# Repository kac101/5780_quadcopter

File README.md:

<h1 align="center">ECE 5780 - Quadcopter</h1>

<p>
Quadcopter Team Members:
<ul style="list-style-position: inside;">
  <li>Rudis Argueta</li>
  <li>Donggeon Kim </li>
  <li>Taehoon Kim</li>
  <li>Luke Stillings </li>
</ul>
</p>

___

<p align="center" style="font-size:11px;">
Figure 1. GIF Of The Drone Hovering
</p>  

---

## Project Summary
A quadcopter that can only hover made using the Raspberry Pi Pico 2 W, a motor driver, BetaFPV motors, and a MPU6050. 

**How It Works:**
To create a quadcopter using the Raspberry Pi Pico 2W we had to create a motor driver that will power the motors by using a battery, and the PWM signals coming from the Raspberry Pi Pico 2W. The PWM signals control the speed of the motors, and to do this we used a MOSFET that has a low threshold voltage because the max voltage the Pico's PWM will be is 3.3V. Additionally, we used a MPU6050 to grab x, and y information, and with this information we created a PID loop that will attempt to keep the quadcopter at a 0° roll, and pitch rate. Additionally, the frame and drone was assembled by us. 

---

## System Architecture

1. **Power**  
   - 1s LiPo battery -> Power 4x BetaFPV Motors  
   - USB Connection Powers Raspberry Pi Pico 2 W 

2. **Sensing**  
   - MPU6050 → I²C (GPIO 26/27)  
   - Data-ready interrupt (GPIO 22) 

3. **Control**  
   - PID loop 
   - PWM on four channels (GPIO 6–9)
   - Data over serial USB
   - Onboard LED blink marks start/end of each loop  

---

## Development Milestones

### Milestone 1  
- Proto-PCB built to verify MOSFET motor-driver circuit  
- Final PCB layout completed (Pico, MOSFETs, IMU)  
- Component selection and documentation finalized

<p align="center" style="font-size:11px;">
Figure 2. Schematic Diagram of the Motor Driver Circuit
</p>

<p align="center" style="font-size:11px;">
Figure 3. Final PCB Layout of our Motor Driver that will control the drone Motors
</p>  

### Milestone 2  
- Assembled & tested PCB + 3D-printed frame  
- Verified PWM control (0 %→75 % duty) and MOSFET switching  
- Eliminated a board-short by redesigning mount  

### Milestone 3  
- I²C MPU6050 integration with drift calibration  
- ADC-based battery monitoring  
- Full system flight test

<p align="center" style="font-size:11px;">
Figure 4. USB Serial Output of Roll Rate, Pitch Rate, and Current Battery Voltage.
</p>  

### Milestone 4
- Demonstation
[Click here to see full demo video](videos_images/IMG_0630.MOV)

---

## Hardware Details

### How Everything is Wired:

The following is how everything is wired together and Figure 5. shows the pinout diagram for the Raspberry Pi Pico 2W.

<p align="center" style="font-size:11px;">
Figure 5. Raspberry Pi Pico 2W pinout.
</p>

#### HiLetGo MPU6050 Connections to Raspberry Pi Pico 2W 
         VCC -> VBUS
         SDA -> I2C1 SCL
         SCL -> I2C1 SDA
         GND -> GND
         INT -> GP22

#### Raspberry Pi Pico 2W connections to Motor Driver PCB
         GP6 -> Motor Drive Motor 1 
         GP7 -> Motor Drive Motor 2
         GP8 -> Motor Drive Motor 3   
         GP9 -> Motor Drive Motor 4
         GND -> GND

#### Voltage Divider Connections to Motor Driver and Raspberry Pi Pico 2W
         VCC -> PWR
         GND -> GND
         Divider Output -> GP28

### Frame & How It Was Made

Figure 6. showcases the first iteration of our drone frame. The second iteration of our frame had the motor holders removed to reduce the weight, and motors were super glued to the frame. 
Also, the HiLetGo MPU6050 was glued to the frame aswell. Between the Raspberry Pi Pico and motor driver, a wood plate was added to prevent short. Lastly, the battery was placed at the bottom bed of the drone and zipped tied. All components were wrapped around by kapton tape to be secured and prevent any shorts when testing/flying.

<p align="center" style="font-size:11px;">
Figure 6. 3D rendering of drone frame made in Fusion 360
</p>

<p align="center" style="font-size:11px;">
Figure 7. Image of the fully completed drone 
</p>

**Motor Spin Direction and Wiring Colors:**
- **Clockwise (CW)**: Motors with **Red and Blue** wires (top right and bottom left)
- **Counterclockwise (CCW)**: Motors with **White and Black** wires (top left and bottom right)

### Component List:
Main:
- 1x Raspberry Pi Pico 2W 
- 1x HiLetGo MPU6050
- 1x Voltage Divider (made with proto board and through-hole resistors)
- 1x Motor Driver (custom motor driver schematic can be found in the schematic folder above)
- 4x BetaFPV Brushed Motors
- 1x Drone Frame (made by us)

Supporting Components:
- 10kΩ Resistor – 0805W8F1002T5E
- 5A Diode – SS54B
- 0.1µF Capacitor – CL05B104KO5NNNC
- MOSFET – AO3400A
- 1µF Capacitor – ESL105M100AC3AA
- JST 2.0 Connector

## Software Details

- **Language & SDK:** C using Pico SDK & Hardware API  
- **Key modules:**  
  - `mpu6050_*` – sensor init, interrupt handler, drift calibration  
  - `pwmSetUp()` – configures 4 PWM slices, sets wrap based on 150 MHz/48 kHz  
  - `pid_control()` – computes motor duty cycles from roll/pitch errors  
  - `Main()` – toggles CYW43 LED, calls PID, prints battery voltage, roll and pitch rates   
- **References:**  
   1. Raspberry Pi Pico 2 W  Datasheet: https://datasheets.raspberrypi.com/picow/pico-2-w-datasheet.pdf
   2. RP2350 - https://datasheets.raspberrypi.com/rp2350/rp2350-datasheet.pdf
   3. Hardware API - https://www.raspberrypi.com/documentation/pico-sdk/hardware.html
   4. MPU-6000 and MPU-6050 Product Specification - https://invensense.tdk.com/wp-content/uploads/2015/02/MPU-6000-Datasheet1.pdf
   5. MPU-6000 and MPU-6050 Register Map and Descriptions - https://invensense.tdk.com/wp-content/uploads/2015/02/MPU-6000-Register-Map1.pdf
   6.  Drone Simulation and Control, Part 2: How Do You Get a Drone to Hover? - https://www.youtube.com/watch?v=GK1t8YIvGM8&t=1s

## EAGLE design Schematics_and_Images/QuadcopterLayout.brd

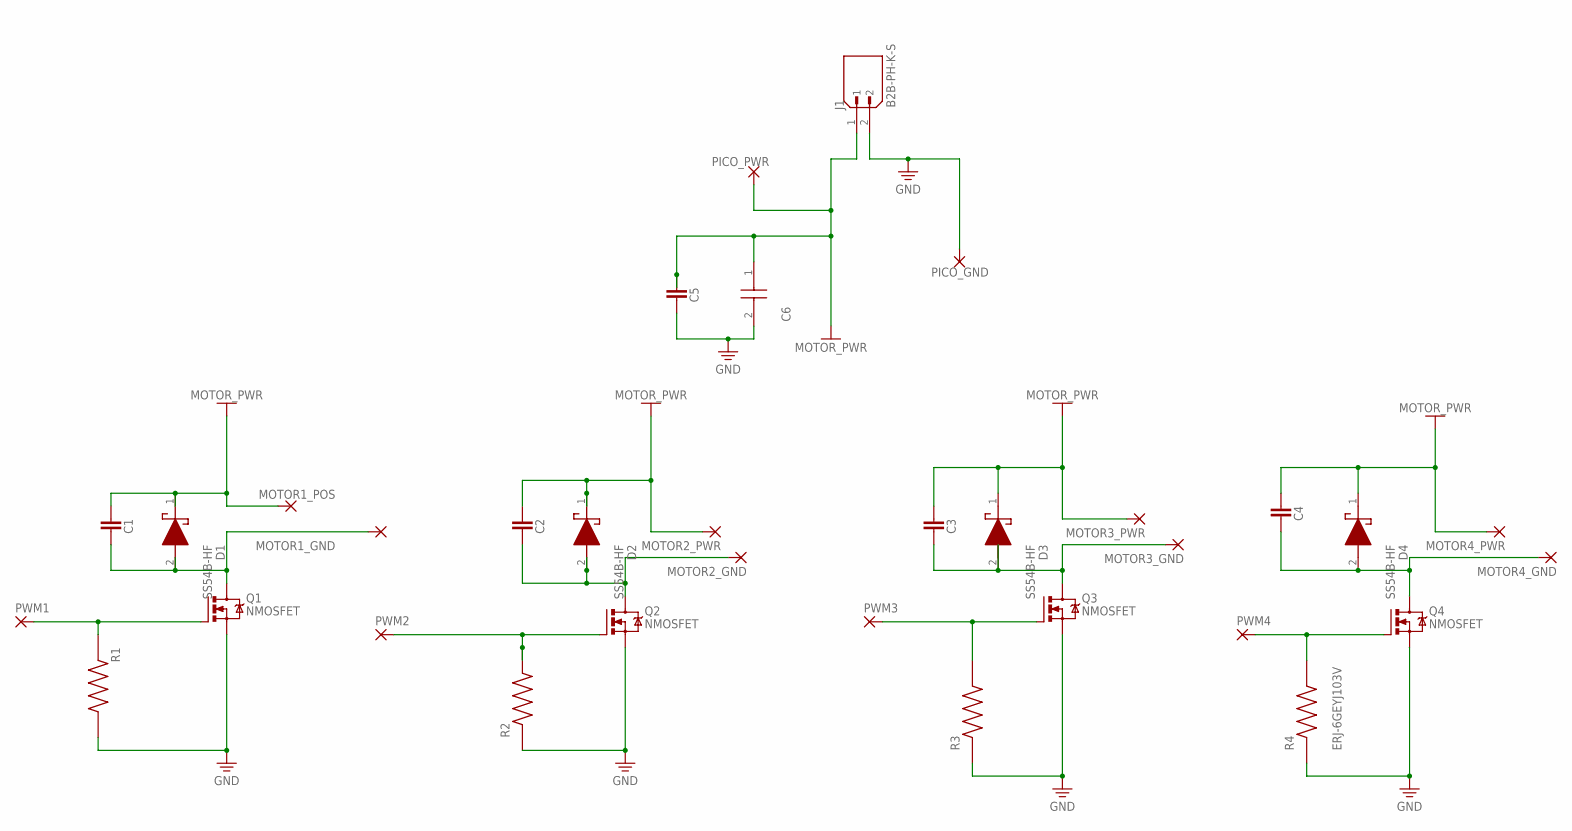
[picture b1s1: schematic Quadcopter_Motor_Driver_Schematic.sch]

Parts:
C1, C2, C3, C4, C5: CAPACITOR_CHIP-0402(1005-METRIC); CAPC1005X60
C6: REA010M2CBK-0511P; CAPPRD200W50D525H1250
D1, D2, D3, D4: SS54B-HF; DIOM5235X244N
J1: B2B-PH-K-S; JST_B2B-PH-K-S
MOTOR1_GND, MOTOR1_POS, MOTOR2_GND, MOTOR2_PWR, MOTOR3_GND, MOTOR3_PWR, MOTOR4_GND, MOTOR4_PWR: 1,6/0,8
PICO_GND: 1,6/0,8
PICO_PWR: 1,6/0,8
PWM1, PWM2, PWM3, PWM4: 1,6/0,8
Q1, Q2, Q3, Q4: NMOSFET; SOT23
R1, R2, R3, R4: ERJ-6GEYJ103V; RES_ERJ-6GEYJ103V

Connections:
+V: C1.2, C2.2, C3.2, C4.2, C5.2, C6.1 (+), D1.1 (K), D2.1 (K), D3.1 (K), D4.1 (K), J1.1, MOTOR1_POS.1, MOTOR2_PWR.1, MOTOR3_PWR.1, MOTOR4_PWR.1, PICO_PWR.1
GND: C5.1, C6.2 (-), J1.2, PICO_GND.1, Q1.2 (S), Q2.2 (S), Q3.2 (S), Q4.2 (S), R1.2, R2.1, R3.1, R4.1
unnamed: C1.1, D1.2 (A), MOTOR1_GND.1, Q1.3 (D)
unnamed: PWM2.1, Q2.1 (G), R2.2
unnamed: PWM1.1, Q1.1 (G), R1.1
unnamed: C3.1, D3.2 (A), MOTOR3_GND.1, Q3.3 (D)
unnamed: C2.1, D2.2 (A), MOTOR2_GND.1, Q2.3 (D)
unnamed: PWM4.1, Q4.1 (G), R4.2
unnamed: C4.1, D4.2 (A), MOTOR4_GND.1, Q4.3 (D)
unnamed: PWM3.1, Q3.1 (G), R3.2

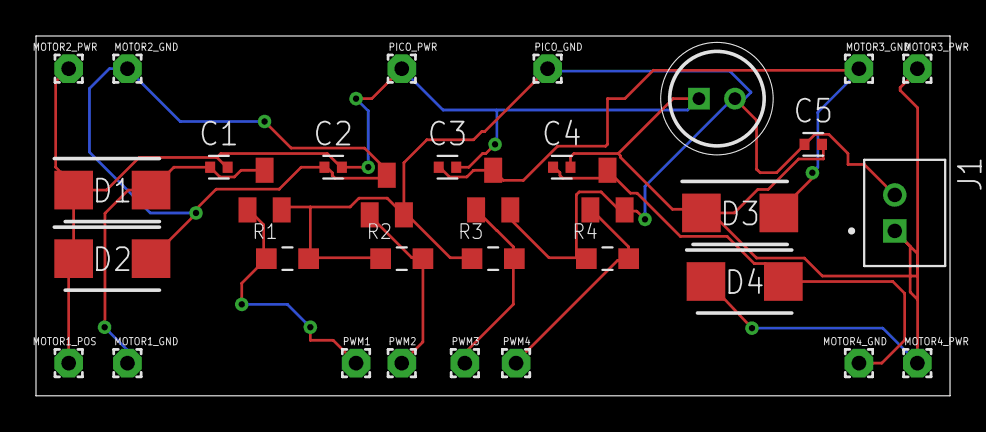
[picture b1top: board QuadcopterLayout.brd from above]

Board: 2 copper layers, 50.8 x 20.0 mm, 33 parts (0 on the bottom side), 10 nets.

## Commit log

2025-03-23 Taehoon Kim
2025-03-25 Added my name to the List
2025-03-28 Add my name
2025-04-03 testing commit_quadcopter_PWM
2025-04-03 PWM based on lab3
2025-04-03 Initial commit with PWM control and build files
2025-04-04 Working on PWM
2025-04-04 Still error
2025-04-04 removed wrong code using c not cpp, and created no file with correct board type
2025-04-04 added hardware pwm lib
2025-04-04 added hardware pwm lib to user requested libraries
2025-04-04 added LED blinking
2025-04-04 Update README.md
    images & videos
2025-04-11 added pin definitions for the pins the are going to be used for PWM
2025-04-11 added code for PWM Set up
2025-04-11 fixed wrong pin names
2025-04-11 added code to cycle through each motor
2025-04-11 added links in comment for websties used
2025-04-11 added comment about increasing speed
2025-04-11 added comment on motor_num and fixed comment for init
2025-04-11 removed comment
2025-04-11 fixed comment
2025-04-12 Remove build directories
2025-04-13 Check MPU6050 WHO_AM_I register
2025-04-13 Read MPU6050 measurement data
2025-04-13 Setup MPU6050 data ready interrupt
2025-04-13 Move MPU6050 startup and measurement into procedures
2025-04-14 Implement simple gyro calibration
2025-04-14 Remove unused MPU6050 register definitions
2025-04-14 Allow recalibration in main loop
2025-04-14 Reset orientation after calibration
2025-04-19 Update pwmDrone.c
    added a function which is named as power
    It can read battery's voltage (ADC)
2025-04-19 Update CMakeLists.txt
    added hardware_adc library
2025-04-20 made pwm set up into its own function
2025-04-20 calling pwm set up in main
2025-04-20 moved all macros/variables for better structure
2025-04-20 changed pwm freq, and comment
2025-04-20 added comments for roll,pitch,yaw
2025-04-20 added comments to tell where the motors are located
2025-04-25 added images and schematics
2025-04-25 removed temp loop
2025-04-25 removed unnecessary code
2025-04-25 added more code for voltage divider reading from ADC
2025-04-25 finished up battery reading code
2025-04-25 changed function name to something more easily understood
2025-04-25 changed to correct pins, and correct adc used
2025-04-25 adjusted comment to be less wordy
2025-04-25 changed to correct pins for I2C
2025-04-25 changed to correct interrupt pin
2025-04-25 added variables for PID control
2025-04-25 added function to clamp values for PID
2025-04-25 added image of serial port outputs
2025-04-25 added PID control, and removed battery function and just added it to main
2025-04-25 fixed and comment and created seperate folder for schematics
2025-04-25 added video of drone hovering
2025-04-25 changed Kp lower
2025-04-25 added GIF just incase video cant be embedded in readme
2025-04-25 readme
2025-04-25 draft
2025-04-26 Drone_Frame used for Demo
    We removed the motor holder parts to reduce the weight and super glued the motors to the frame.
    Also, gyro MPU 6050 was glued to the frame. Between Pi Pico and motor driver, we added a wood plate to prevent short.
    Battery was placed at the bottom bed of this drone and cable tied.
2025-04-26 Drone image
    Drone image showing how it was all put together
2025-04-26 Functioin diagram
    It is a function diagram, showing how components are connected
2025-04-26 Pi Pico2W
    This is showing which pins are what
2025-04-26 Pico2w pin
2025-04-26 screenshot version because stl cant be seen in readme
2025-04-26 Update README.md
    Readme added figures
2025-04-26 added correct video reference
2025-04-26 fixed up readme
2025-04-26 removed
2025-04-26 removed incorrect heading
2025-04-26 corrected mistakes
2025-04-26 added some more info
2025-04-26 changed image sizes
2025-04-26 changed GIF size
2025-04-26 moved list name out of the list
2025-04-26 added centering alligning
2025-04-26 removed centering
2025-04-26 added line
2025-04-26 fixed grammar
2025-04-26 added more helpful comments
2025-04-26 added motor direction image
2025-04-26 Update README.md
    added motor spin direction info and added list of componetns too
2025-04-26 Fix figure labels and numbers
2025-04-26 MP4 version instead of MOV
    same demo vidoe instead it is MP4
